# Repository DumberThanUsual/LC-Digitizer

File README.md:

# LC Resonator Locator and Digitizer

## Second Year Group Project Hardware Element

This project is the hardware input element of my second year FPGA group project. 
The FPGA part was a hardware accelerated complex function plotter, taking coordinates of poles and zeros on the complex plane as inputs and displaying the result on an HDMI display.
The input hardware is a board that detects the positions of tokens that represent poles and zeros of different orders which can be placed on the board.

## Theory of Operation

The tokens are a capacitor and inductor in paralell, forming an LC resonator. The inductor is unshielded, allowing it to interact with external magnetic fields. 
They can be caused to resonate by an electromagnetic impulse generated by placing it on a coil and sending a pusle of current through it. 
The presence of the token can be detected by measuring the voltage on the coil after the original impulse and looking for the resonant frequency of the resonator.

Using this for detection and location of the tokens can be done by separating and multiplexing the detection loops into transmission and reception loops.
These loops can be elongated and placed perpendicularly on opposite sides of a PCB. Pulsing one Tx loop and listening on all Rx loops measures token presence on one row and scanning all Tx coils reveals the entire plane.

Measurement of tokens not located exactly within one intersection (cell) of Tx and Rx coils is done by measuring the amplitude of a cluster of responses and adjusting the final position proportionally. 
This requires the minimum spacing between tokens to be greater than twice the width of the coils.

Differentiating between types of tokens, representing differing orders of the poles and zeros, is done by varying the resonant frequencies of the tokens and measuring this in the response.

## Issues and Reflections

This project was designed with little time for development and refinement. The PCB had to be ordered within 2 weeks of the project start, with no second revision. This means there are some (very questionable) quirks in the design, including:
- "Row Amplifers": After some debate, we did not want to risk the expected sub-millivolt signal being lost in the multiplexers. To be safe, we added a 20dB amplifier for every row.
  Not only was the signal much larger than measured in the prototype, but the multiplexers do not affect the signal in a meaningful way. The capacitor between the gain-setting resistors and the reference is not necessary and nor is the entire row amplifier circuit.
  This saves 8 ICs, lots of board space and some cost.

- Slow loop driver ICs: The loop driver ICs are pulsed by pulsing their sleep pins, not the input pins. We did not read the datasheet properly - these ICs take 30µs to wake from sleep.
  Given this needs to be done 128 times per scan, at multiple scans per second, this is a big limiting factor in the update rate.
  Instead, the sleep pins should be tied low and the OE pins on the shift registers be pulsed instead.

- Slow OLED: The oled is of the I2C variety, running at 400kHz. Using a non-DMA library to drive it, this is very slow and stops the UI task from properly reading the rotary encoder inputs.

- Suicidal power managment: If there is a glitch in the power supply, it seems to be possible that the shift registers and driver ICs can be set to drive a loop, shorting the supply to ground and browning out the µC and preventing it from turning off the drivers.
  This does not cause damage to the board, but the power needs to be recycled before it will work again and is very annoying.

- Substandard firmware: The firmware became progressivly more rushed as time went on. This is especially visible in the liberal use of ```nop``` delays instead of proper freeRTOS and timer delays.

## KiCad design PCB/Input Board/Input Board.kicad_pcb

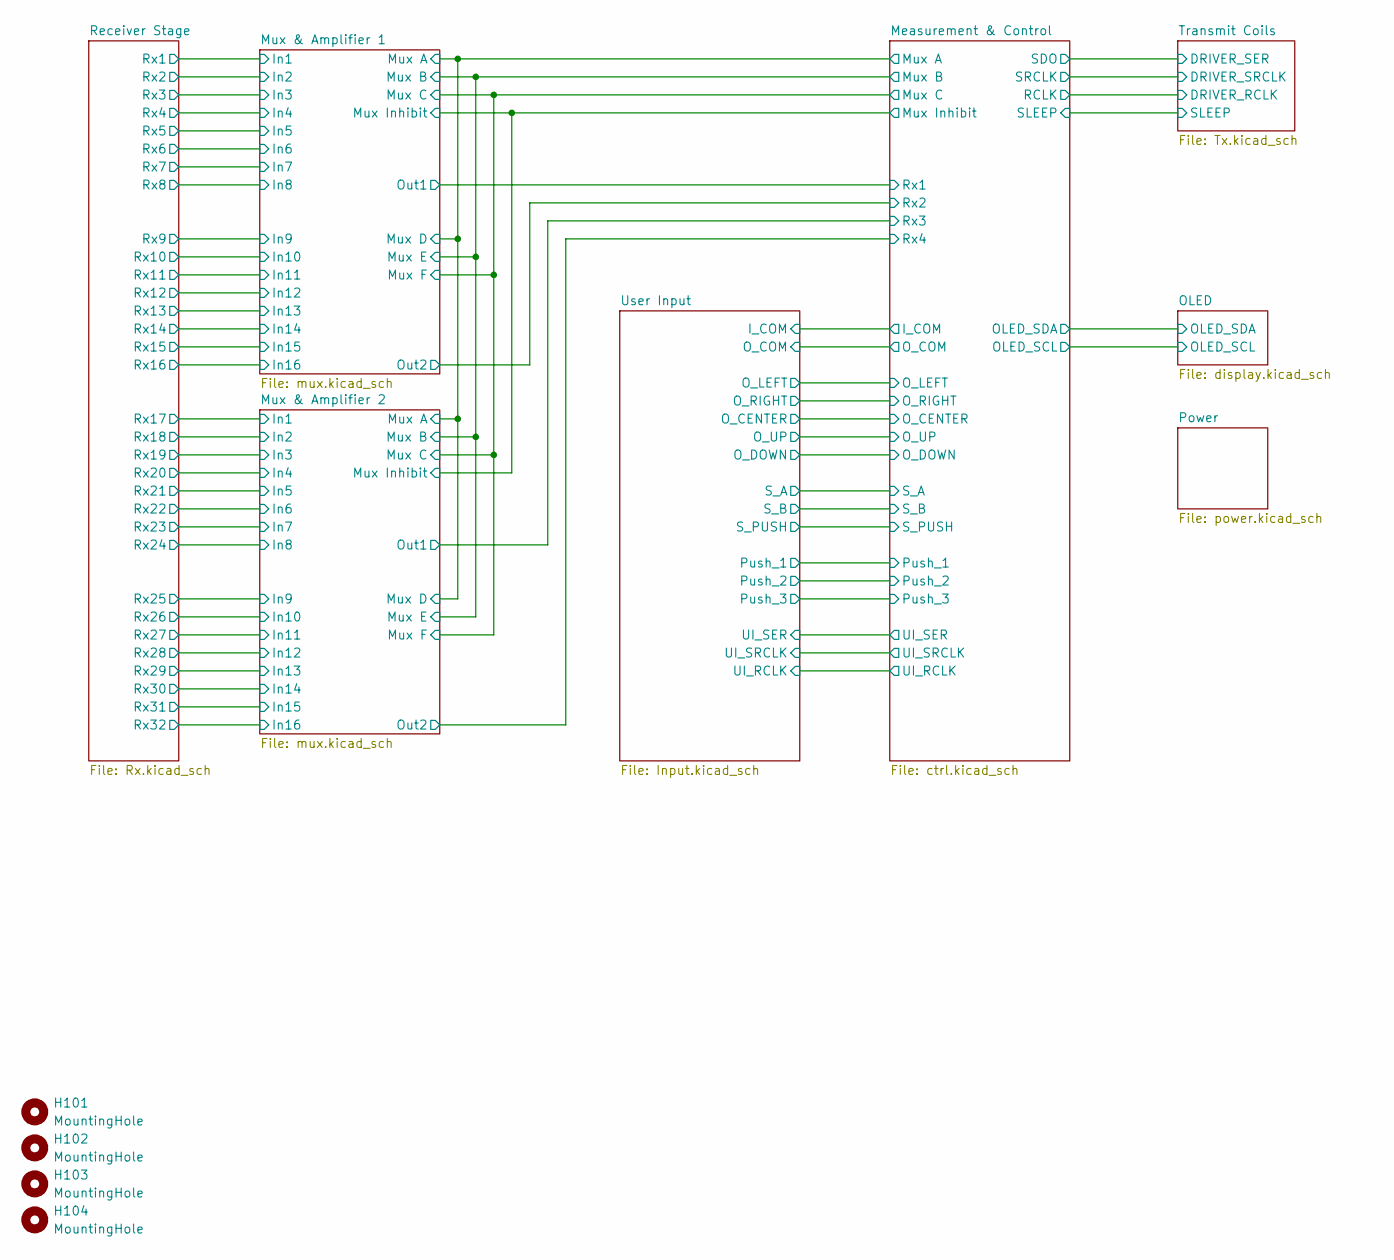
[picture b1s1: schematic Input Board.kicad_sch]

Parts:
H101, H102, H103, H104: MountingHole; MountingHole_3.2mm_M3

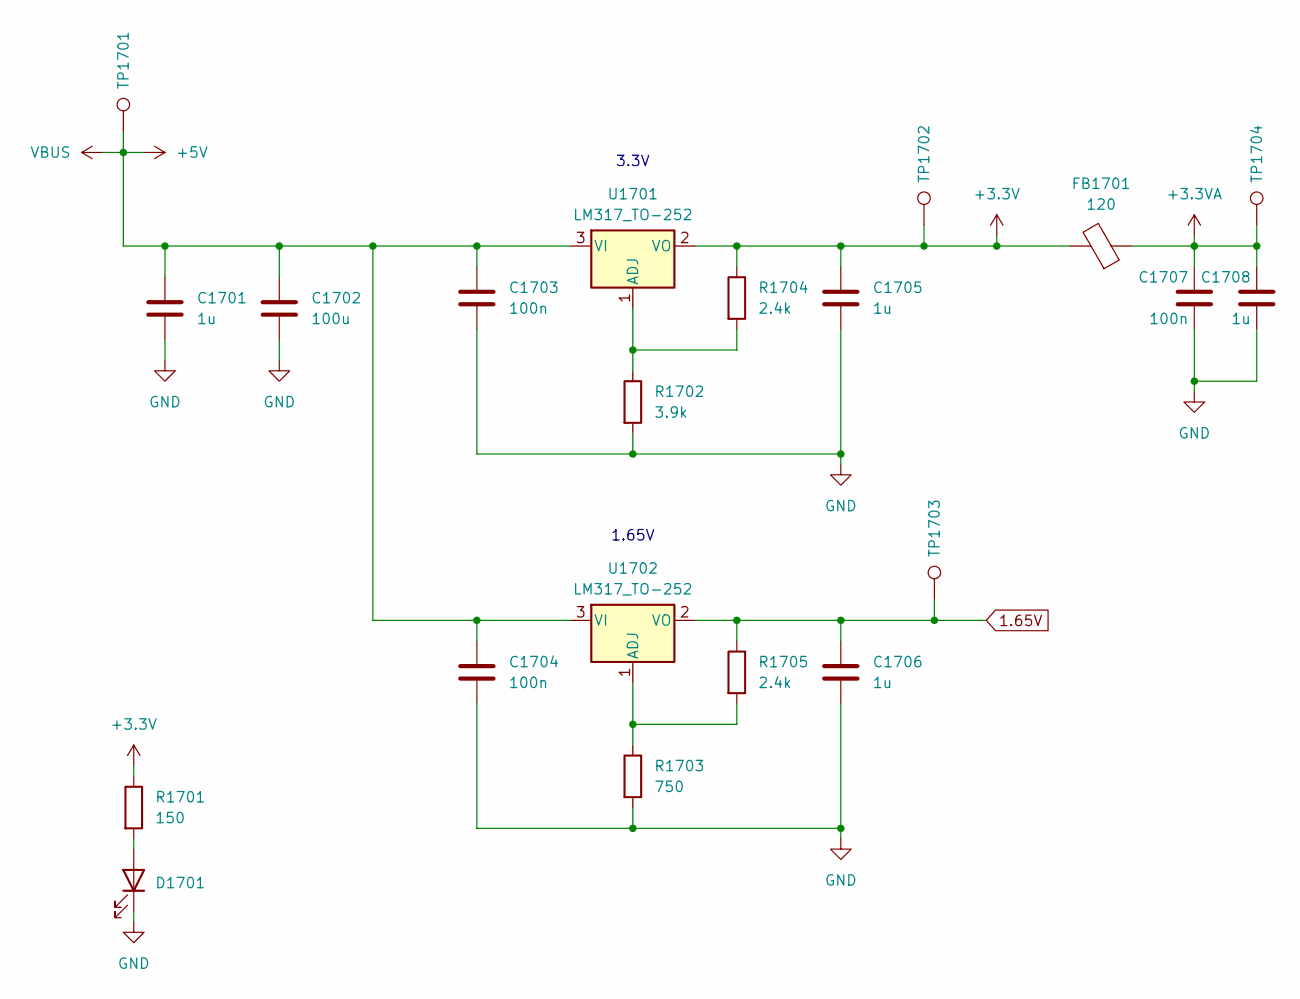
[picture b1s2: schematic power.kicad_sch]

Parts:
C1701, C1705, C1706: 1u; C_0603_1608Metric
C1702: 100u; C_Elec_4x5.8
C1703, C1704: 100n; C_0603_1608Metric
C1707: 100n; C_0603_1608Metric; Manufacturer Part Number CL05B104KB54PNC; JLC Part Type Basic
C1708: 1u; C_0603_1608Metric; Manufacturer Part Number CL21B105KBFNNNE; JLC Part Type Basic
D1701: LED_0603_1608Metric
FB1701: 120; L_1206_3216Metric
R1701: 150; R_0603_1608Metric
R1702: 3.9k; R_0603_1608Metric
R1703: 750; R_0603_1608Metric
R1704, R1705: 2.4k; R_0603_1608Metric
TP1701, TP1702, TP1703, TP1704: TestPoint; TestPoint_Pad_1.5x1.5mm
U1701, U1702: LM317_TO-252; SOT-89-3

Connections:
1.65V: C1706.1, R1705.1, TP1703.1, U1702.2 (VO); also elsewhere on the board
+3.3V: C1705.1, FB1701.2, R1701.1, R1704.1, TP1702.1, U1701.2 (VO); also elsewhere on the board
+3.3VA: C1707.1, C1708.1, FB1701.1, TP1704.1; also elsewhere on the board
+5V: C1701.1, C1702.1, C1703.1, C1704.1, TP1701.1, U1701.3 (VI), U1702.3 (VI); also elsewhere on the board
GND: C1701.2, C1702.2, C1703.2, C1704.2, C1705.2, C1706.2, C1707.2, C1708.2, D1701.1 (K), R1702.2, R1703.2; also elsewhere on the board
unnamed: D1701.2 (A), R1701.2
unnamed: R1702.1, R1704.2, U1701.1 (ADJ)
unnamed: R1703.1, R1705.2, U1702.1 (ADJ)

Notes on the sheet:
1.65V
3.3V

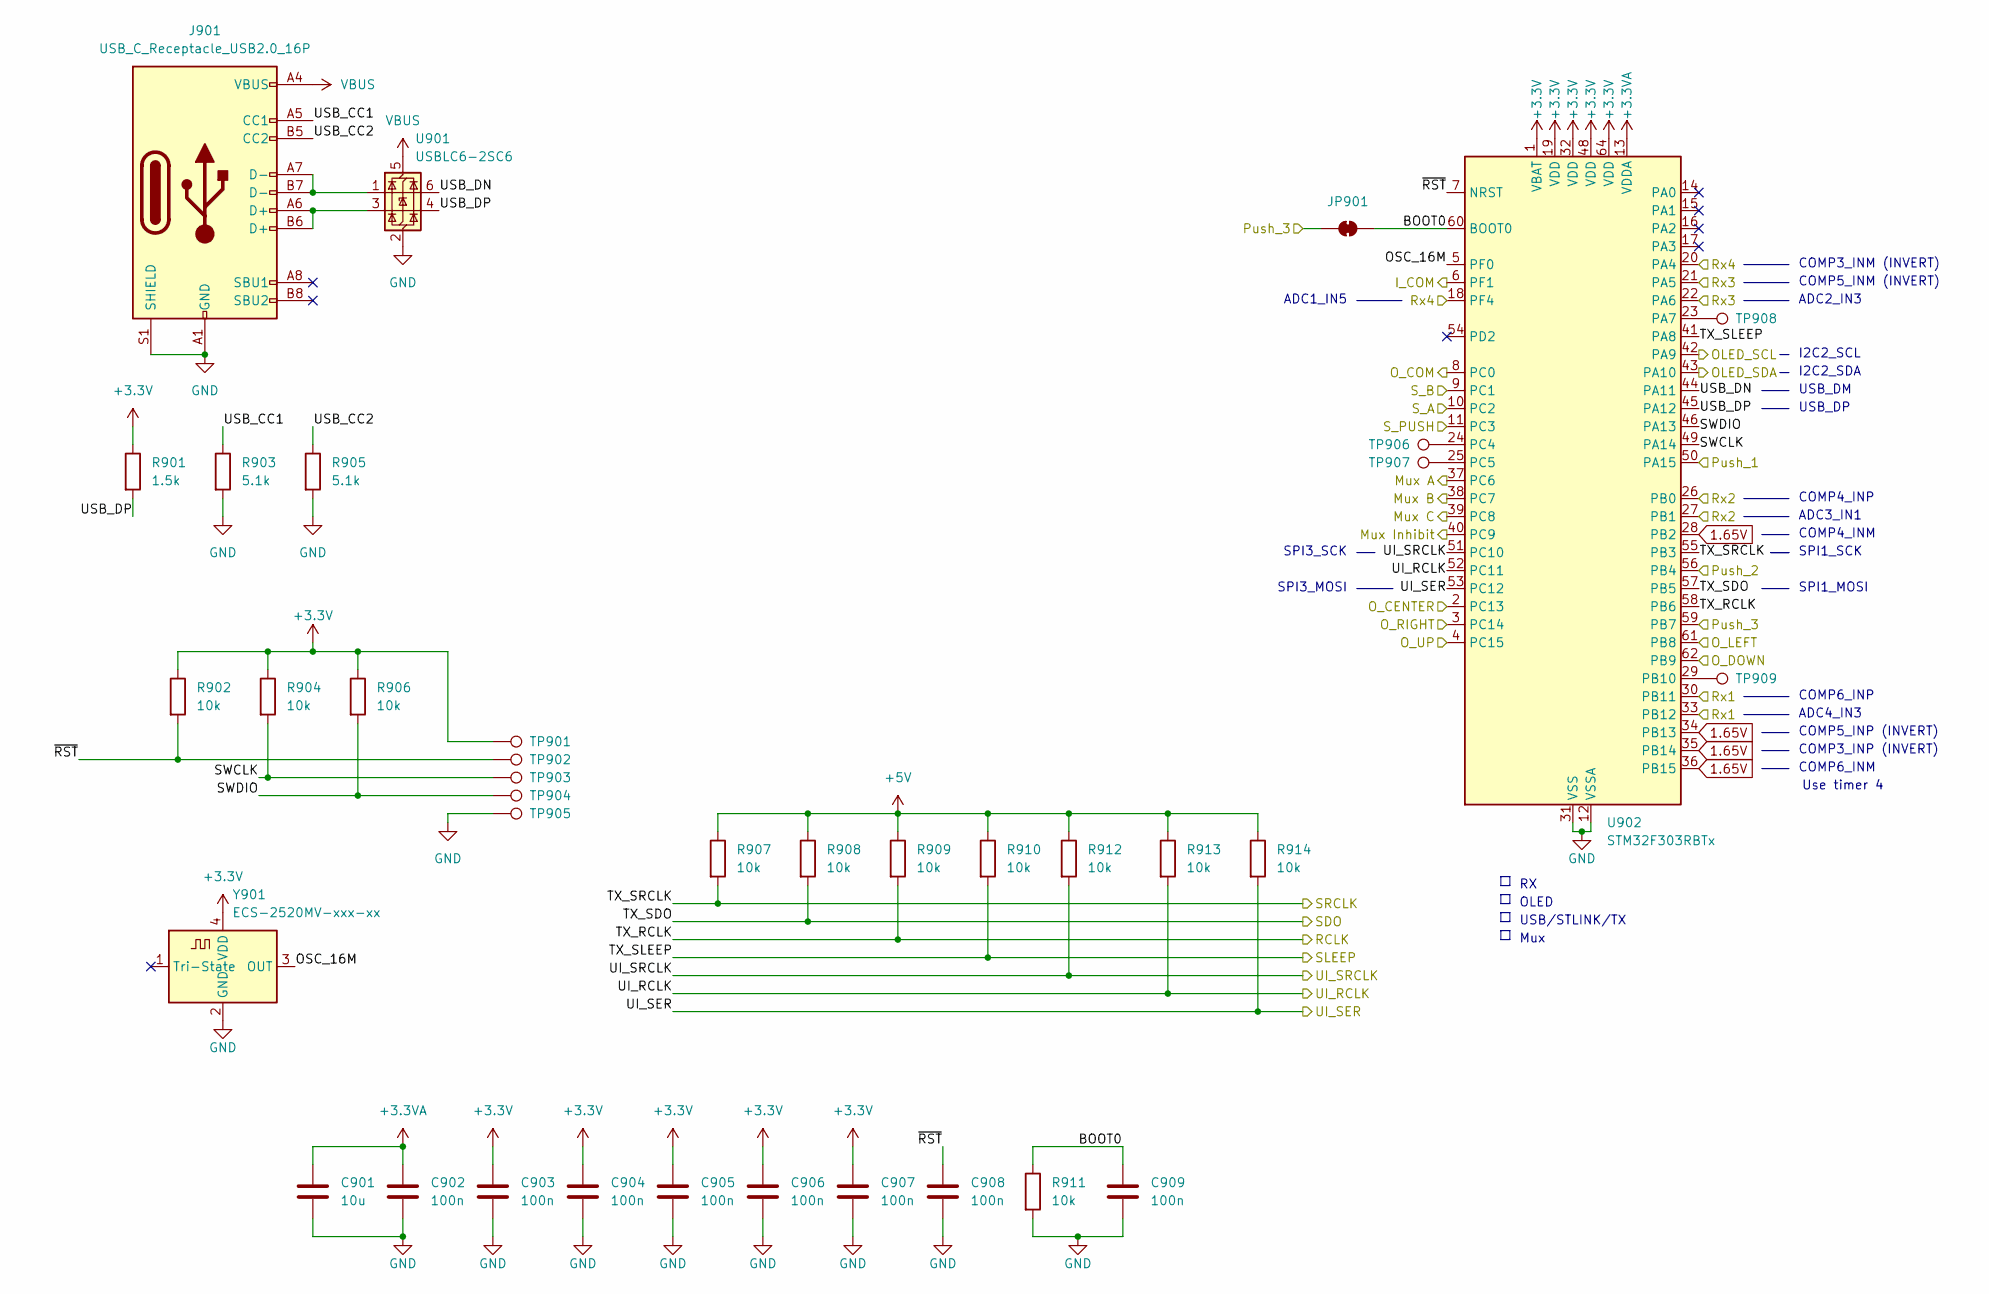
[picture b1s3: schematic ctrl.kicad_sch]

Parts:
C901: 10u; C_0603_1608Metric
C902, C903, C904, C905, C906, C907, C908, C909: 100n; C_0603_1608Metric
J901: USB_C_Receptacle_USB2.0_16P; USB_C_Receptacle_GCT_USB4110
JP901: SolderJumper_2_Bridged; SolderJumper-2_P1.3mm_Bridged_RoundedPad1.0x1.5mm
R901: 1.5k; R_0603_1608Metric
R902, R904, R906, R907, R908, R909, R910, R911, R912, R913, R914: 10k; R_0603_1608Metric
R903, R905: 5.1k; C_0603_1608Metric
TP901, TP902, TP903, TP904, TP905, TP906, TP907, TP908, TP909: TestPoint; TestPoint_Pad_1.5x1.5mm
U901: USBLC6-2SC6; SOT-23-6
U902: STM32F303RBTx; LQFP-64_10x10mm_P0.5mm
Y901: ECS-2520MV-xxx-xx; Oscillator_SMD_ECS_2520MV-xxx-xx-4Pin_2.5x2.0mm

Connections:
1.65V: U902.28 (PB2), U902.34 (PB13), U902.35 (PB14), U902.36 (PB15); also elsewhere on the board
+3.3V: C903.1, C904.1, C905.1, C906.1, C907.1, R901.1, R902.1, R904.1, R906.1, TP901.1, U902.1 (VBAT), U902.19 (VDD), U902.32 (VDD), U902.48 (VDD), U902.64 (VDD), Y901.4 (VDD); also elsewhere on the board
+3.3VA: C901.1, C902.1, U902.13 (VDDA); also elsewhere on the board
+5V: J901.A4 (VBUS), J901.A9 (VBUS), J901.B4 (VBUS), J901.B9 (VBUS), R907.1, R908.1, R909.1, R910.1, R912.1, R913.1, R914.1, U901.5 (VBUS); also elsewhere on the board
/Measurement & Control/BOOT0: C909.1, JP901.2 (B), R911.1, U902.60 (BOOT0)
/Measurement & Control/I_COM: U902.6 (PF1); also elsewhere on the board
/Measurement & Control/Mux A: U902.37 (PC6); also elsewhere on the board
/Measurement & Control/Mux B: U902.38 (PC7); also elsewhere on the board
/Measurement & Control/Mux C: U902.39 (PC8); also elsewhere on the board
/Measurement & Control/Mux Inhibit: U902.40 (PC9); also elsewhere on the board
/Measurement & Control/OLED_SCL: U902.42 (PA9); also elsewhere on the board
/Measurement & Control/OLED_SDA: U902.43 (PA10); also elsewhere on the board
/Measurement & Control/OSC_16M: U902.5 (PF0), Y901.3 (OUT)
/Measurement & Control/O_CENTER: U902.2 (PC13); also elsewhere on the board
/Measurement & Control/O_COM: U902.8 (PC0); also elsewhere on the board
/Measurement & Control/O_DOWN: U902.62 (PB9); also elsewhere on the board
/Measurement & Control/O_LEFT: U902.61 (PB8); also elsewhere on the board
/Measurement & Control/O_RIGHT: U902.3 (PC14); also elsewhere on the board
/Measurement & Control/O_UP: U902.4 (PC15); also elsewhere on the board
/Measurement & Control/Push_1: U902.50 (PA15); also elsewhere on the board
/Measurement & Control/Push_2: U902.56 (PB4); also elsewhere on the board
/Measurement & Control/Push_3: JP901.1 (A), U902.59 (PB7); also elsewhere on the board
/Measurement & Control/Rx1: U902.30 (PB11), U902.33 (PB12); also elsewhere on the board
/Measurement & Control/Rx2: U902.26 (PB0), U902.27 (PB1); also elsewhere on the board
/Measurement & Control/Rx3: U902.21 (PA5), U902.22 (PA6); also elsewhere on the board
/Measurement & Control/Rx4: U902.18 (PF4), U902.20 (PA4); also elsewhere on the board
/Measurement & Control/SWCLK: R904.2, TP903.1, U902.49 (PA14)
/Measurement & Control/SWDIO: R906.2, TP904.1, U902.46 (PA13)
/Measurement & Control/S_A: U902.10 (PC2); also elsewhere on the board
/Measurement & Control/S_B: U902.9 (PC1); also elsewhere on the board
/Measurement & Control/S_PUSH: U902.11 (PC3); also elsewhere on the board
/Measurement & Control/TX_RCLK: R909.2, U902.58 (PB6); also elsewhere on the board
/Measurement & Control/TX_SDO: R908.2, U902.57 (PB5); also elsewhere on the board
/Measurement & Control/TX_SLEEP: R910.2, U902.41 (PA8); also elsewhere on the board
/Measurement & Control/TX_SRCLK: R907.2, U902.55 (PB3); also elsewhere on the board
/Measurement & Control/UI_RCLK: R913.2, U902.52 (PC11); also elsewhere on the board
/Measurement & Control/UI_SER: R914.2, U902.53 (PC12); also elsewhere on the board
/Measurement & Control/UI_SRCLK: R912.2, U902.51 (PC10); also elsewhere on the board
/Measurement & Control/USB_CC1: J901.A5 (CC1), R903.1
/Measurement & Control/USB_CC2: J901.B5 (CC2), R905.1
/Measurement & Control/USB_DN: U901.6 (I/O1), U902.44 (PA11)
/Measurement & Control/USB_DP: R901.2, U901.4 (I/O2), U902.45 (PA12)
/Measurement & Control/~RST: C908.1, R902.2, TP902.1, U902.7 (NRST)
GND: C901.2, C902.2, C903.2, C904.2, C905.2, C906.2, C907.2, C908.2, C909.2, J901.A1 (GND), J901.A12 (GND), J901.B1 (GND), J901.B12 (GND), J901.S1 (SHIELD), R903.2, R905.2, R911.2, TP905.1, U901.2 (GND), U902.12 (VSSA), U902.31 (VSS), U902.47 (VSS), U902.63 (VSS), Y901.2 (GND); also elsewhere on the board
unnamed: J901.A6 (D+), J901.B6 (D+), U901.3 (I/O2)
unnamed: J901.A7 (D-), J901.B7 (D-), U901.1 (I/O1)
unnamed: TP908.1, U902.23 (PA7)
unnamed: TP909.1, U902.29 (PB10)
unnamed: TP906.1, U902.24 (PC4)
unnamed: TP907.1, U902.25 (PC5)

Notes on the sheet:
SPI3_SCK
SPI1_MOSI
COMP5_INM (INVERT)
ADC4_IN3
COMP3_INP (INVERT)
ADC3_IN1
COMP5_INP (INVERT)
COMP4_INP
I2C2_SCL
SPI1_SCK
ADC2_IN3
COMP3_INM (INVERT)
USB_DP
USB/STLINK/TX
COMP6_INP
ADC1_IN5
COMP4_INM
Use timer 4
SPI3_MOSI
OLED
Mux
USB_DM
COMP6_INM
I2C2_SDA

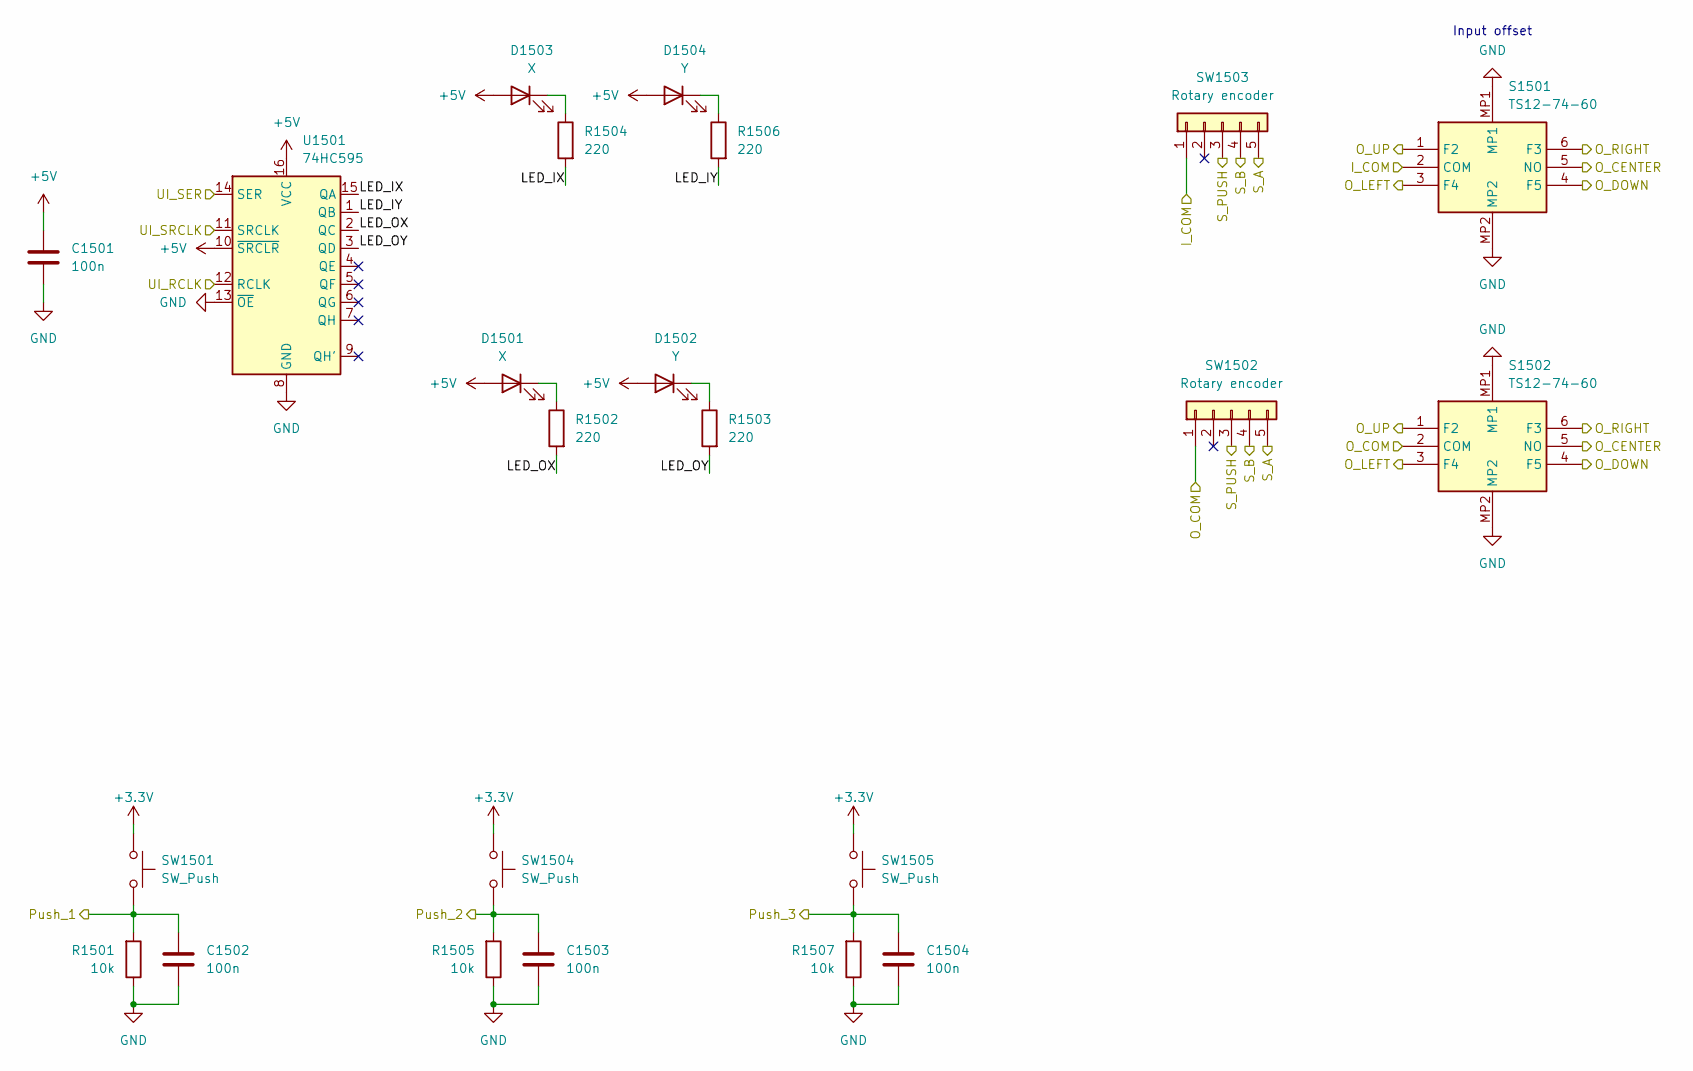
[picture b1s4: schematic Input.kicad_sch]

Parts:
C1501, C1502, C1503, C1504: 100n; C_0603_1608Metric
D1501, D1503: X; LED_0603_1608Metric
D1502, D1504: Y; LED_0603_1608Metric
R1501, R1505, R1507: 10k; R_0603_1608Metric
R1502, R1503, R1504, R1506: 220; R_0603_1608Metric
S1501, S1502: TS12-74-60; TS127460; Mouser Part Number 179-TS127460250SMTTR
SW1501, SW1504, SW1505: SW_Push; SW_SPST_B3S-1000
SW1502, SW1503: Rotary encoder; Untitled
U1501: 74HC595; DHVQFN-16-1EP_2.5x3.5mm_P0.5mm_EP1x2mm

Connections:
+3.3V: SW1501.1, SW1504.1, SW1505.1; also elsewhere on the board
+5V: C1501.1, D1501.2 (A), D1502.2 (A), D1503.2 (A), D1504.2 (A), U1501.10 (~SRCLR), U1501.16 (VCC); also elsewhere on the board
/Measurement & Control/I_COM: S1501.2 (COM), SW1503.1; also elsewhere on the board
/Measurement & Control/O_CENTER: S1501.5 (NO), S1502.5 (NO); also elsewhere on the board
/Measurement & Control/O_COM: S1502.2 (COM), SW1502.1; also elsewhere on the board
/Measurement & Control/O_DOWN: S1501.4 (F5), S1502.4 (F5); also elsewhere on the board
/Measurement & Control/O_LEFT: S1501.3 (F4), S1502.3 (F4); also elsewhere on the board
/Measurement & Control/O_RIGHT: S1501.6 (F3), S1502.6 (F3); also elsewhere on the board
/Measurement & Control/O_UP: S1501.1 (F2), S1502.1 (F2); also elsewhere on the board
/Measurement & Control/Push_1: C1502.1, R1501.2, SW1501.2; also elsewhere on the board
/Measurement & Control/Push_2: C1503.1, R1505.2, SW1504.2; also elsewhere on the board
/Measurement & Control/Push_3: C1504.1, R1507.2, SW1505.2; also elsewhere on the board
/Measurement & Control/S_A: SW1502.5, SW1503.5; also elsewhere on the board
/Measurement & Control/S_B: SW1502.4, SW1503.4; also elsewhere on the board
/Measurement & Control/S_PUSH: SW1502.3, SW1503.3; also elsewhere on the board
/Measurement & Control/UI_RCLK: U1501.12 (RCLK); also elsewhere on the board
/Measurement & Control/UI_SER: U1501.14 (SER); also elsewhere on the board
/Measurement & Control/UI_SRCLK: U1501.11 (SRCLK); also elsewhere on the board
/User Input/LED_IX: R1504.2, U1501.15 (QA)
/User Input/LED_IY: R1506.2, U1501.1 (QB)
/User Input/LED_OX: R1502.2, U1501.2 (QC)
/User Input/LED_OY: R1503.2, U1501.3 (QD)
GND: C1501.2, C1502.2, C1503.2, C1504.2, R1501.1, R1505.1, R1507.1, S1501.MP1, S1501.MP2, S1502.MP1, S1502.MP2, U1501.8 (GND), U1501.13 (~OE), U1501.17; also elsewhere on the board
unnamed: D1501.1 (K), R1502.1
unnamed: D1502.1 (K), R1503.1
unnamed: D1503.1 (K), R1504.1
unnamed: D1504.1 (K), R1506.1

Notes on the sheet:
Input offset

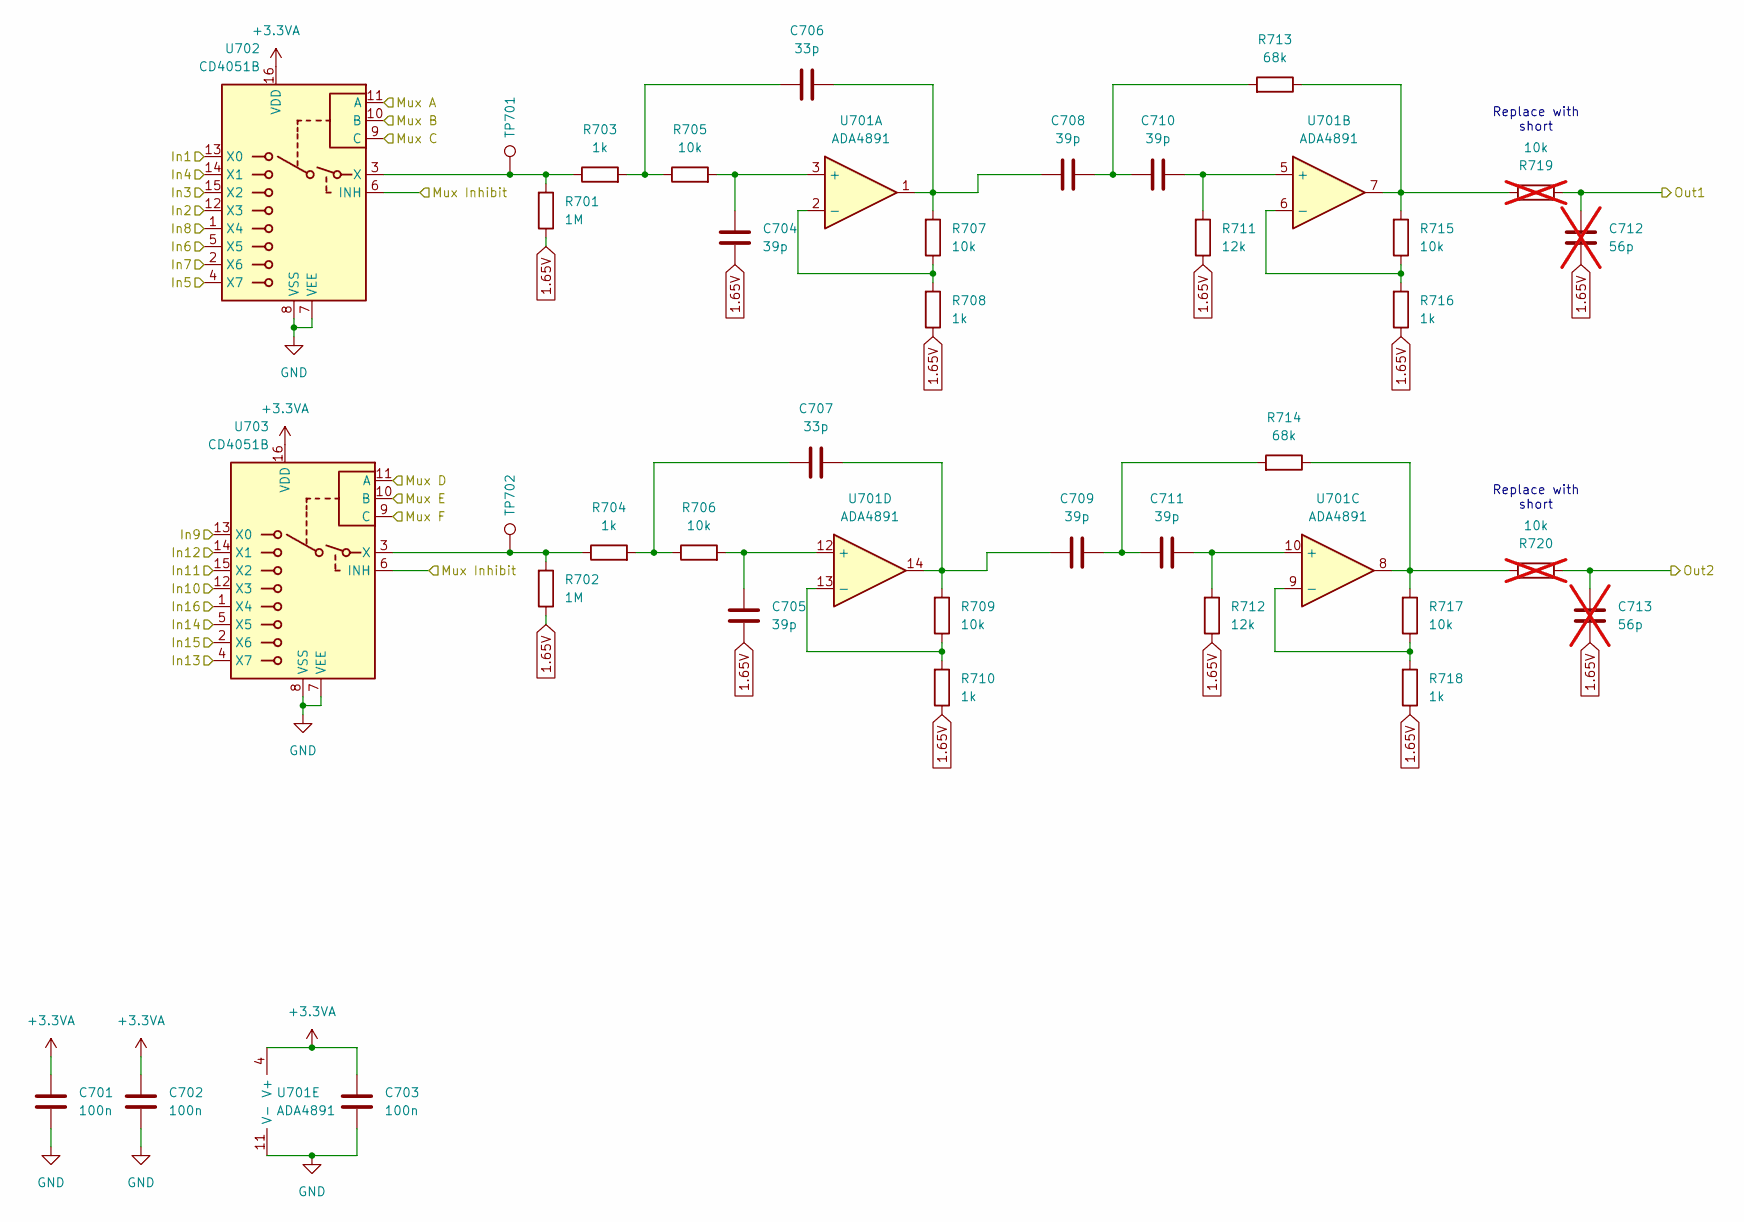
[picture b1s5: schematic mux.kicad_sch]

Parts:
C701, C702, C703: 100n; C_0603_1608Metric
C704, C705, C708, C709, C710, C711: 39p; C_0603_1608Metric
C706, C707: 33p; C_0603_1608Metric
C712, C713: 56p; C_0603_1608Metric; not fitted
R701, R702: 1M; R_0603_1608Metric
R703, R704, R708, R710, R716, R718: 1k; R_0603_1608Metric
R705, R706, R707, R709, R715, R717: 10k; R_0603_1608Metric
R711, R712: 12k; R_0603_1608Metric
R713, R714: 68k; R_0603_1608Metric
R719, R720: 10k; R_0603_1608Metric; not fitted
TP701, TP702: TestPoint; TestPoint_Pad_1.5x1.5mm
U701: ADA4891; SOIC-14_3.9x8.7mm_P1.27mm
U702, U703: CD4051B; SOIC-16_3.9x9.9mm_P1.27mm

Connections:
1.65V: C704.2, C705.2, C712.1, C713.1, R701.1, R702.1, R708.1, R710.1, R711.1, R712.1, R716.1, R718.1; also elsewhere on the board
+3.3VA: C701.1, C702.1, C703.1, U701.4 (V+), U702.16 (VDD), U703.16 (VDD); also elsewhere on the board
/Measurement & Control/Mux A: U702.11 (A), U703.11 (A); also elsewhere on the board
/Measurement & Control/Mux B: U702.10 (B), U703.10 (B); also elsewhere on the board
/Measurement & Control/Mux C: U702.9 (C), U703.9 (C); also elsewhere on the board
/Measurement & Control/Mux Inhibit: U702.6 (INH), U703.6 (INH); also elsewhere on the board
/Measurement & Control/Rx1: C712.2, R719.1; also elsewhere on the board
/Measurement & Control/Rx2: C713.2, R720.1; also elsewhere on the board
/Mux & Amplifier 1/In1: U702.13 (X0); also elsewhere on the board
/Mux & Amplifier 1/In2: U702.12 (X3); also elsewhere on the board
/Mux & Amplifier 1/In3: U702.15 (X2); also elsewhere on the board
/Mux & Amplifier 1/In4: U702.14 (X1); also elsewhere on the board
/Mux & Amplifier 1/In5: U702.4 (X7); also elsewhere on the board
/Mux & Amplifier 1/In6: U702.5 (X5); also elsewhere on the board
/Mux & Amplifier 1/In7: U702.2 (X6); also elsewhere on the board
/Mux & Amplifier 1/In8: U702.1 (X4); also elsewhere on the board
/Mux & Amplifier 1/In9: U703.13 (X0); also elsewhere on the board
/Mux & Amplifier 1/In10: U703.12 (X3); also elsewhere on the board
/Mux & Amplifier 1/In11: U703.15 (X2); also elsewhere on the board
/Mux & Amplifier 1/In12: U703.14 (X1); also elsewhere on the board
/Mux & Amplifier 1/In13: U703.4 (X7); also elsewhere on the board
/Mux & Amplifier 1/In14: U703.5 (X5); also elsewhere on the board
/Mux & Amplifier 1/In15: U703.2 (X6); also elsewhere on the board
/Mux & Amplifier 1/In16: U703.1 (X4); also elsewhere on the board
GND: C701.2, C702.2, C703.2, U701.11 (V-), U702.7 (VEE), U702.8 (VSS), U703.7 (VEE), U703.8 (VSS); also elsewhere on the board
unnamed: C706.1, R703.2, R705.1
unnamed: C706.2, C708.1, R707.2, U701.1
unnamed: C707.1, R704.2, R706.1
unnamed: C707.2, C709.1, R709.2, U701.14
unnamed: C708.2, C710.1, R713.2
unnamed: C709.2, C711.1, R714.2
unnamed: R713.1, R715.2, R719.2, U701.7
unnamed: R714.1, R717.2, R720.2, U701.8
unnamed: C704.1, R705.2, U701.3 (+)
unnamed: R707.1, R708.2, U701.2 (-)
unnamed: C710.2, R711.2, U701.5 (+)
unnamed: R715.1, R716.2, U701.6 (-)
unnamed: C711.2, R712.2, U701.10 (+)
unnamed: R717.1, R718.2, U701.9 (-)
unnamed: C705.1, R706.2, U701.12 (+)
unnamed: R709.1, R710.2, U701.13 (-)
unnamed: R701.2, R703.1, TP701.1, U702.3 (X)
unnamed: R702.2, R704.1, TP702.1, U703.3 (X)

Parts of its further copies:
C801, C802, C803: 100n; C_0603_1608Metric
C804, C805, C808, C809, C810, C811: 39p; C_0603_1608Metric
C806, C807: 33p; C_0603_1608Metric
C812, C813: 56p; C_0603_1608Metric; not fitted
R801, R802: 1M; R_0603_1608Metric
R803, R804, R808, R810, R816, R818: 1k; R_0603_1608Metric
R805, R806, R807, R809, R815, R817: 10k; R_0603_1608Metric
R811, R812: 12k; R_0603_1608Metric
R813, R814: 68k; R_0603_1608Metric
R819, R820: 10k; R_0603_1608Metric; not fitted
TP801, TP802: TestPoint; TestPoint_Pad_1.5x1.5mm
U801: ADA4891; SOIC-14_3.9x8.7mm_P1.27mm
U802, U803: CD4051B; SOIC-16_3.9x9.9mm_P1.27mm

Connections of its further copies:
1.65V: C804.2, C805.2, C812.1, C813.1, R801.1, R802.1, R808.1, R810.1, R811.1, R812.1, R816.1, R818.1; also elsewhere on the board
+3.3VA: C801.1, C802.1, C803.1, U801.4 (V+), U802.16 (VDD), U803.16 (VDD); also elsewhere on the board
/Measurement & Control/Mux A: U802.11 (A), U803.11 (A); also elsewhere on the board
/Measurement & Control/Mux B: U802.10 (B), U803.10 (B); also elsewhere on the board
/Measurement & Control/Mux C: U802.9 (C), U803.9 (C); also elsewhere on the board
/Measurement & Control/Mux Inhibit: U802.6 (INH), U803.6 (INH); also elsewhere on the board
/Measurement & Control/Rx3: C812.2, R819.1; also elsewhere on the board
/Measurement & Control/Rx4: C813.2, R820.1; also elsewhere on the board
/Mux & Amplifier 2/In1: U802.13 (X0); also elsewhere on the board
/Mux & Amplifier 2/In2: U802.12 (X3); also elsewhere on the board
/Mux & Amplifier 2/In3: U802.15 (X2); also elsewhere on the board
/Mux & Amplifier 2/In4: U802.14 (X1); also elsewhere on the board
/Mux & Amplifier 2/In5: U802.4 (X7); also elsewhere on the board
/Mux & Amplifier 2/In6: U802.5 (X5); also elsewhere on the board
/Mux & Amplifier 2/In7: U802.2 (X6); also elsewhere on the board
/Mux & Amplifier 2/In8: U802.1 (X4); also elsewhere on the board
/Mux & Amplifier 2/In9: U803.13 (X0); also elsewhere on the board
/Mux & Amplifier 2/In10: U803.12 (X3); also elsewhere on the board
/Mux & Amplifier 2/In11: U803.15 (X2); also elsewhere on the board
/Mux & Amplifier 2/In12: U803.14 (X1); also elsewhere on the board
/Mux & Amplifier 2/In13: U803.4 (X7); also elsewhere on the board
/Mux & Amplifier 2/In14: U803.5 (X5); also elsewhere on the board
/Mux & Amplifier 2/In15: U803.2 (X6); also elsewhere on the board
/Mux & Amplifier 2/In16: U803.1 (X4); also elsewhere on the board
GND: C801.2, C802.2, C803.2, U801.11 (V-), U802.7 (VEE), U802.8 (VSS), U803.7 (VEE), U803.8 (VSS); also elsewhere on the board
unnamed: C806.1, R803.2, R805.1
unnamed: C806.2, C808.1, R807.2, U801.1
unnamed: C807.1, R804.2, R806.1
unnamed: C807.2, C809.1, R809.2, U801.14
unnamed: C808.2, C810.1, R813.2
unnamed: C809.2, C811.1, R814.2
unnamed: R813.1, R815.2, R819.2, U801.7
unnamed: R814.1, R817.2, R820.2, U801.8
unnamed: C804.1, R805.2, U801.3 (+)
unnamed: R807.1, R808.2, U801.2 (-)
unnamed: C810.2, R811.2, U801.5 (+)
unnamed: R815.1, R816.2, U801.6 (-)
unnamed: C811.2, R812.2, U801.10 (+)
unnamed: R817.1, R818.2, U801.9 (-)
unnamed: C805.1, R806.2, U801.12 (+)
unnamed: R809.1, R810.2, U801.13 (-)
unnamed: R801.2, R803.1, TP801.1, U802.3 (X)
unnamed: R802.2, R804.1, TP802.1, U803.3 (X)

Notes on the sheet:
Replace with short

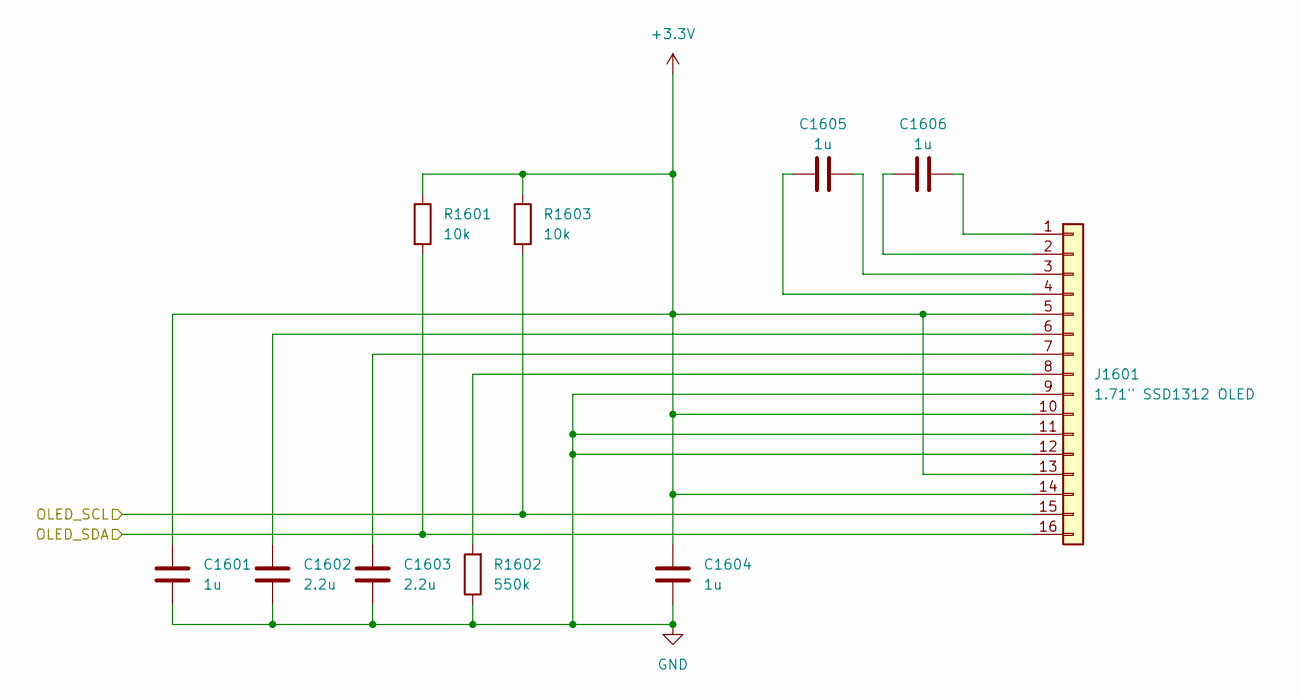
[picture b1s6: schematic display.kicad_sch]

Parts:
C1601, C1604: 1u; C_0603_1608Metric
C1602, C1603: 2.2u; C_0603_1608Metric
C1605, C1606: 1u; C_0603_1608Metric; Rating 10V
J1601: 1.71" SSD1312 OLED; 1.71 OLED SSD1312
R1601, R1603: 10k; R_0603_1608Metric
R1602: 550k; R_0603_1608Metric

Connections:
+3.3V: C1601.1, C1604.1, J1601.5, J1601.10, J1601.13, J1601.14, R1601.1, R1603.1; also elsewhere on the board
/Measurement & Control/OLED_SCL: J1601.15, R1603.2; also elsewhere on the board
/Measurement & Control/OLED_SDA: J1601.16, R1601.2; also elsewhere on the board
GND: C1601.2, C1602.2, C1603.2, C1604.2, J1601.9, J1601.11, J1601.12, R1602.1; also elsewhere on the board
unnamed: C1606.2, J1601.1
unnamed: C1606.1, J1601.2
unnamed: C1605.2, J1601.3
unnamed: C1605.1, J1601.4
unnamed: C1602.1, J1601.6
unnamed: C1603.1, J1601.7
unnamed: J1601.8, R1602.2
